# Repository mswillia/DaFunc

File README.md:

DaFunc
======

Trinket Pro based portable function generator

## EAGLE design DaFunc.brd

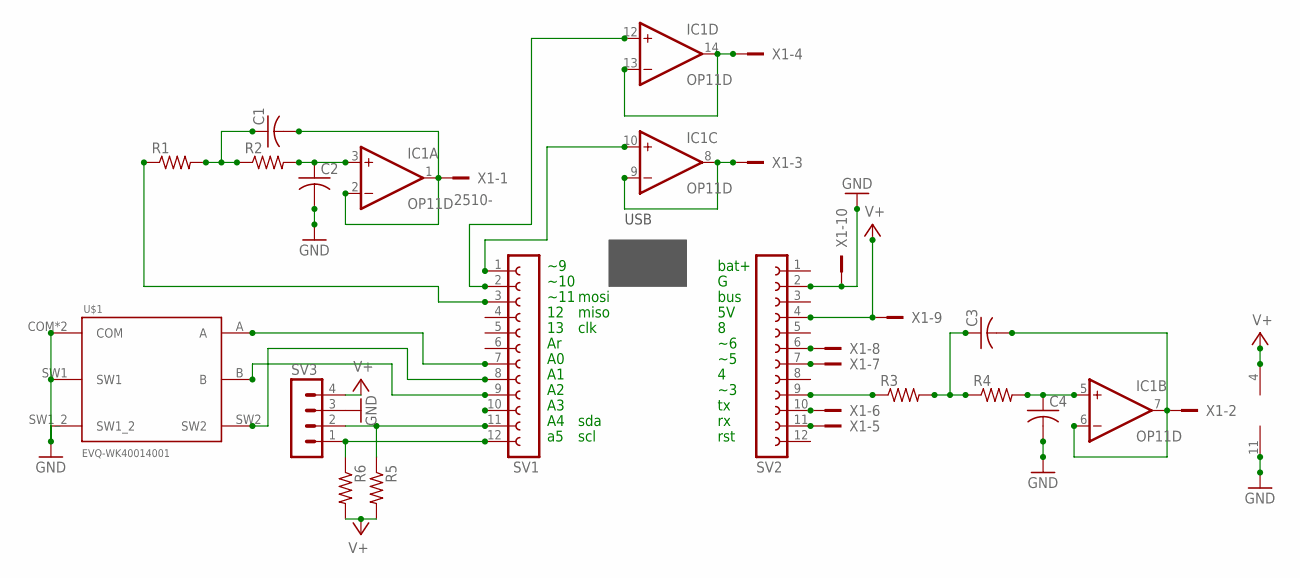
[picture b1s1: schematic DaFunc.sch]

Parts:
C1, C2, C3, C4: C-USC0603; C0603
IC1: OP11D; SO14
R1, R2, R3, R4, R5, R6: R-US_R0603; R0603
SV1, SV2: FE12-1; FE12
SV3: MA04-1
U$1: EVQ-WK40014001; WK4
X1: 2510-; PAK100/2500-10

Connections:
GND: C2.2, C4.2, IC1.11 (V-), SV2.2, SV3.3, U$1.COM, U$1.GND (COM), U$1.SW1, U$1.SW1_2, X1.10
unnamed: C1.1, R1.2, R2.1
unnamed: C2.1, IC1.3 (+IN), R2.2
unnamed: R6.1, SV1.12, SV3.1
unnamed: R5.1, SV1.11, SV3.2
unnamed: SV1.9, U$1.B
unnamed: SV1.8, U$1.SW2
unnamed: SV1.7, U$1.A
unnamed: R1.1, SV1.3
unnamed: IC1.10 (+IN), SV1.1
unnamed: SV2.11, X1.5
unnamed: SV2.10, X1.6
unnamed: R3.1, SV2.9
unnamed: SV2.7, X1.7
unnamed: SV2.6, X1.8
unnamed: C4.1, IC1.5 (+IN), R4.2
unnamed: C3.1, R3.2, R4.1
unnamed: IC1.8 (OUT), IC1.9 (-IN), X1.3
unnamed: C3.2, IC1.6 (-IN), IC1.7 (OUT), X1.2
unnamed: C1.2, IC1.1 (OUT), IC1.2 (-IN), X1.1
unnamed: IC1.13 (-IN), IC1.14 (OUT), X1.4
unnamed: IC1.12 (+IN), SV1.2
V+: IC1.4 (V+), R5.2, R6.2, SV2.4, SV3.4, X1.9

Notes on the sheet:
bat+
rst
bus
~10
~11
mosi
miso
clk
sda
scl
USB

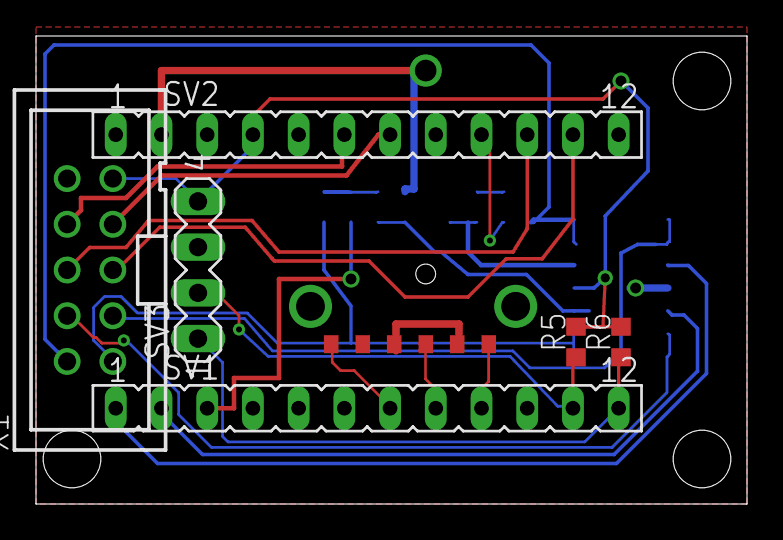
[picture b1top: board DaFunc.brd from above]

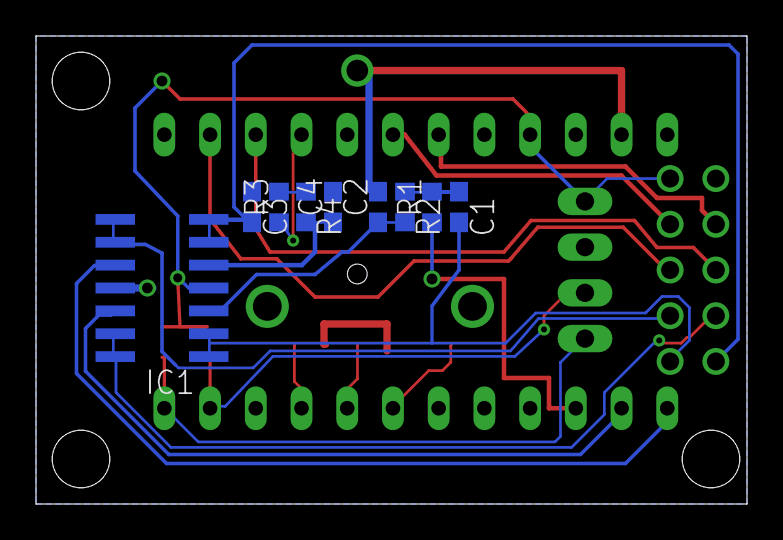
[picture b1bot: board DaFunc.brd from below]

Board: 2 copper layers, 39.5 x 26.0 mm, 16 parts (9 on the bottom side), 23 nets.

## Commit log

2015-01-02 Initial commit of current setup.
